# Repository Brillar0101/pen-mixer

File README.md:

# Pen Mixer

Pen Mixer is a small motion controller that clips onto the top of an ordinary
pen and turns handwriting gestures into live audio control. An IMU on the
board reads tilt and twist, an nRF52840 sends the motion to a laptop over
Bluetooth, and the laptop shapes whatever track is playing: tilt the pen and
a filter sweeps, twist it and the level moves. The better your pen control
gets, the better your mix sounds.

<p align="center"><em>The v2.1 board (13 &times; 35 mm) in its clear case</em></p>

This repo holds the whole project: prototype firmware, production firmware and
laptop stack, and the production PCB as a KiCad project.

```mermaid
flowchart LR
    HAND["Hand<br>tilt, twist"] --> FW

    subgraph pen["Pen Mixer board: on the pen"]
        FW["LSM6DS3TR-C IMU<br>+ ISP1807 nRF52840"]
    end

    FW -->|"BLE, Nordic UART"| BR
    FW -.->|"USB-C, serial"| BR

    subgraph laptop["Laptop"]
        BR["bridge.py<br>smooth, map"] -->|"UDP"| PD["Pure Data<br>filter + gain"]
        BR -->|"SSE"| DASH["dashboard<br>localhost:8080"]
    end

    PD --> SPK["Speakers"]

    classDef pfBlue fill:#E7F1FA,stroke:#0066CC,color:#151515
    classDef pfGold fill:#FDF7E7,stroke:#F0AB00,color:#151515
    classDef pfGreen fill:#F3FAF2,stroke:#3E8635,color:#151515
    classDef pfGray fill:#F0F0F0,stroke:#6A6E73,color:#151515
    class HAND,SPK pfBlue
    class FW pfGreen
    class BR pfGold
    class PD,DASH pfGray
```

## The hardware

Two production board shapes exist. v2.1 is a 13 x 35 mm bar (frozen in
`production/kicad/v2/`). v3, the current design in `production/kicad/`, is a
regular five-point star 40 mm tip to tip with a vertical, top-entry USB-C
(G-Switch GT-USB-7055E) in the body so all five prongs are identical, the
antenna at the top tip, LEDs out on the left arm and the button in the right
arm; otherwise the same parts and the same four-layer 0.8 mm stack. The v2.1 board is a 13 x 35 mm, four-layer, 0.8 mm PCB, all SMD, designed
to ride on a pen barrel with a 401230 LiPo at the back of the pen.

| Ref | Part | Role |
|---|---|---|
| U1 | ISP1807 | nRF52840 with integrated antenna, pre-certified |
| U2 | LSM6DS3TR-C | 6-axis IMU |
| U3 | MCP73831 | LiPo charger, 50 mA |
| U4 | TPS7A02 | 3.3 V LDO, 200 nA quiescent |
| J1 | USB-C 16P | charge, programming, serial |
| J2 | pads on B.Cu | off-board LiPo, 401230 |

The KiCad project lives in `production/`. Schematic PDF, board plots, a render
and the BOM are in `production/output/`.

The board is fully routed and fabrication-ready: 0 unrouted connections,
ground pours on all four layers, and a clean DRC. U1 sits on the official
JLCPCB land pattern with part-for-part verified pad geometry, and every
component carries the 3D model of the exact part being ordered.

Every pinout came from a primary datasheet, kept in `production/datasheets/`.
The one that would have cost a board spin: ISP1807 pin 20 (OUT_ANT) must be
tied to pin 22 (OUT_MOD) on the application PCB, or the radio has no antenna.

## The firmware and laptop stack

`prototype/` runs on the Seeed XIAO nRF52840 Sense today and targets the
custom board unchanged, since both are an nRF52840 with an ST IMU on I2C.

```
prototype/
  bridge.py           serial or BLE, then smoothing, mapping, UDP, dashboard
  ble_source.py       laptop-side BLE client for --ble
  dashboard.py        live web view on :8080
  firmware/
    code.py           IMU over USB serial
    code_ble.py       IMU over BLE, advertises as PenMixer-Lexy
  patches/            Pure Data: track playback, manual sliders, live input
```

How to run all of it, from firmware to Pure Data to the dashboard, lives in
[docs/RUNNING.md](docs/RUNNING.md).

## Run the desktop app

The Qt app in `app/` is the laptop side: it EQs whatever the computer is
playing, driven by the pen over Bluetooth. Full detail, Docker, and
troubleshooting are in `app/README.md`; the short version:

### macOS

```bash
brew install blackhole-2ch switchaudio-osx       # first time only
git clone https://github.com/Brillar0101/pen-mixer.git
cd pen-mixer/app
python3 -m venv venv
venv/bin/pip install -r requirements.txt -e .    # first time only
venv/bin/python -m penmixer.app                  # every time
```

In the window: click "Route system audio here", set Source to "Bluetooth
(pen board)" or use "Scan Bluetooth", play music, move the pen. Closing the
app restores your speakers.

### Windows

First time only, in an administrator PowerShell, then reboot (VB-CABLE is
the Windows loopback device):

```powershell
curl.exe -L -o $env:TEMP\vbcable.zip https://download.vb-audio.com/Download_CABLE/VBCABLE_Driver_Pack45.zip
Expand-Archive $env:TEMP\vbcable.zip $env:TEMP\vbcable -Force
& $env:TEMP\vbcable\VBCABLE_Setup_x64.exe
shutdown /r /t 0
```

Then in a normal PowerShell:

```powershell
git clone https://github.com/Brillar0101/pen-mixer.git
cd pen-mixer\app
python -m venv venv
venv\Scripts\pip install -r requirements.txt -e .   # first time only
venv\Scripts\python -m penmixer.app                 # every time
```

Set Settings > System > Sound > Output to "CABLE Input", then in the window
click "Hear music here", set Source to "Bluetooth (pen board)", play music,
move the pen. Set the output back to your speakers when done.

No board? Set Source to "Simulate (no board)".

## Measured, not estimated

| What | Number |
|---|---|
| Frame rate over USB | 197 Hz against a 250 Hz target |
| Frames in the soak run | 105,872, 0 malformed |
| Smoother settling, alpha 0.4 | 24 ms to 95% of a step |
| End-to-end budget | 32 ms, against ~20 ms where feel degrades |
| BLE vs USB link cost | ~10 ms vs 1 ms |

## Layout

```
prototype/            nRF52840 Sense build: real IMU, USB or BLE, laptop stack
app/                  Qt desktop app: 3-band EQ, visualizer, one-window stack
                      (start instructions for macOS and Windows: app/README.md)
production/           the production board
  kicad/              KiCad 10 project, footprints, 3D models
  datasheets/         primary sources for every pinout
  output/             schematic PDF, board plots, render, BOM, DRC report
docs/                 architecture, run guide, requirements (PRD)
ARCHITECTURE.md       how it all fits together, with diagrams
```

## License

MIT. See [LICENSE](LICENSE).

Built by Barakaeli ([Brillar0101](https://github.com/Brillar0101)) and
Lexy ([vnllagoldfish](https://github.com/vnllagoldfish)).

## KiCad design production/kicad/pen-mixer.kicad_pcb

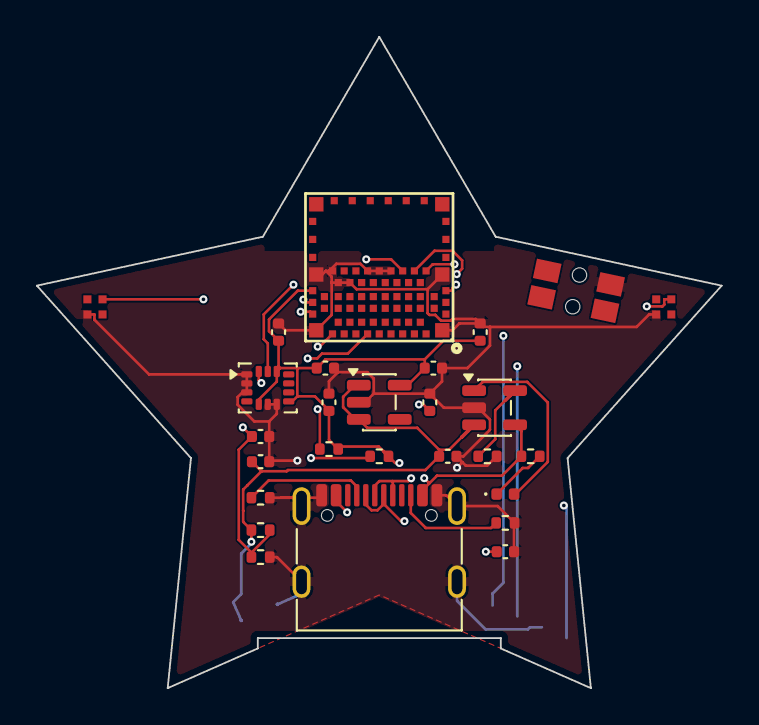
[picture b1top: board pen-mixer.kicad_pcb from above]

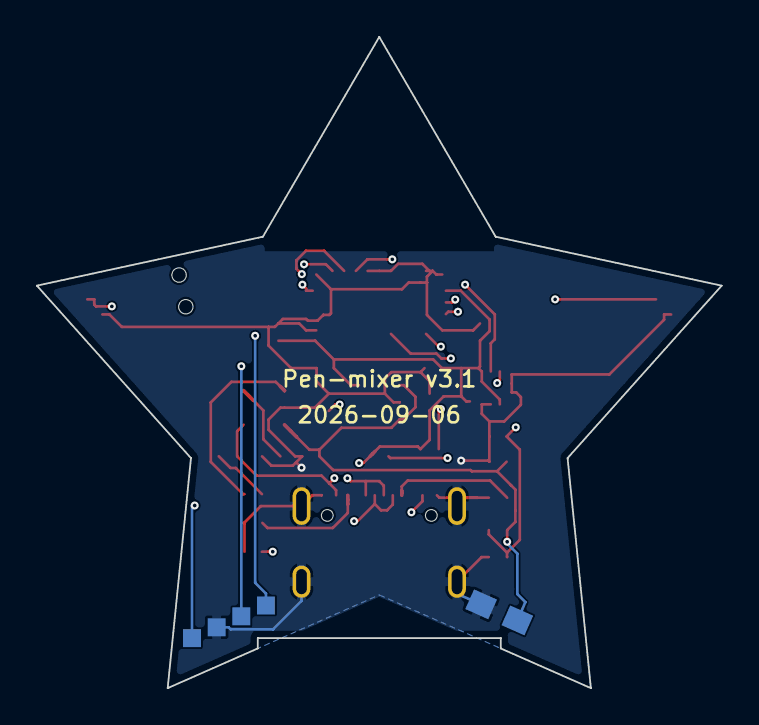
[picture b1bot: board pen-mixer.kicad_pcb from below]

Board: 4 copper layers, 38.0 x 36.2 mm, 32 parts (5 on the bottom side), 16 nets.

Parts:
C1, C2: 4u7; C_0402_1005Metric
C3, C4: 1u; C_0402_1005Metric
C5, C7, C8, C10, C11: 100n; C_0402_1005Metric
C6: 10u; C_0402_1005Metric
D1: GRN; LED_0402_1005Metric
J1: USB-C 16P; GT-USB-7010ASV
J2: BAT; SolderPad_1.2x2.0mm
LED1, LED2: XL-1010RGBC; LED-SMD_4P-L1.0-W1.0-TL_XL-1010RGBC-WS2812B
R1, R2: 5k1; R_0402_1005Metric
R3: 20k; R_0402_1005Metric
R4: 1k; R_0402_1005Metric
R6, R7: 4k7; R_0402_1005Metric
R8, R9: 1M; R_0402_1005Metric
SW1: EVQP7C01P; SW-SMD_EVQP7C01P
TP1: SWDIO; TestPad_1.0mm
TP2: SWDCLK; TestPad_1.0mm
TP4: GND; TestPad_1.0mm
TP5: +3V3; TestPad_1.0mm
U1: ISP1807-LR; BULETM-SMD_ISP1807
U2: LSM6DS3TR-C; LGA-14_3x2.5mm_P0.5mm_LayoutBorder3x4y
U3: MCP73831T-2ACI/OT; SOT-23-5
U4: TPS7A0533PDBV; SOT-23-5

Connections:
+3V3: C4.1, C5.1, C6.1, C7.1, C8.1, R6.2, R7.2, TP5.1, U1.26, U2.5, U2.8, U2.12, U4.5
CC1: J1.A5, R1.1
CC2: J1.B5, R2.1
CHG_STAT: D1.2, U3.1
GND: C1.2, C2.2, C3.2, C4.2, C5.2, C6.2, C7.2, C8.2, C10.2, C11.2, J1.A1, J1.A12, J1.B1, J1.B12, J1.SH, J2.2, LED1.3, LED2.3, R1.2, R2.2, R3.2, R9.2, SW1.2, TP4.1, U1.1, U1.7, U1.14, U1.16, U1.18, U1.21, U1.23, U1.24, U1.25, U1.31, U2.1, U2.2, U2.3, U2.6, U2.7, U3.2, U4.2
IPROG: R3.1, U3.5
LED_A: D1.1, R4.2
SCL: R7.1, U1.6, U2.13
SDA: R6.1, U1.32, U2.14
SWDCLK: TP2.1, U1.30
SWDIO: TP1.1, U1.28
USB_DM: J1.A7, J1.B7, U1.10
USB_DP: J1.A6, J1.B6, U1.8
VBAT: C2.1, C3.1, C11.1, J2.1, LED1.2, LED2.2, R8.1, U3.3, U4.1, U4.3
VBAT_SENSE: C10.1, R8.2, R9.1, U1.38
VBUS: C1.1, J1.A4, J1.A9, J1.B4, J1.B9, R4.1, U1.12, U3.4

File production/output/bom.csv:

"Reference","Value","Footprint","QUANTITY"
"C1,C2","4u7","Capacitor_SMD:C_0402_1005Metric","2"
"C3,C4","1u","Capacitor_SMD:C_0402_1005Metric","2"
"C5,C7-C10","100n","Capacitor_SMD:C_0402_1005Metric","5"
"C6","10u","Capacitor_SMD:C_0402_1005Metric","1"
"D1","GRN","LED_SMD:LED_0402_1005Metric","1"
"J1","USB-C 16P","Connector_USB:USB_C_Receptacle_G-Switch_GT-USB-7010ASV","1"
"J2","BAT","pen-mixer:SolderPad_1.2x2.0mm","1"
"J3","FSR","pen-mixer:SolderPad_1.2x2.0mm","1"
"R1,R2","5k1","Resistor_SMD:R_0402_1005Metric","2"
"R3","20k","Resistor_SMD:R_0402_1005Metric","1"
"R4","1k","Resistor_SMD:R_0402_1005Metric","1"
"R5","10k","Resistor_SMD:R_0402_1005Metric","1"
"R6,R7","4k7","Resistor_SMD:R_0402_1005Metric","2"
"R8,R9","1M","Resistor_SMD:R_0402_1005Metric","2"
"TP1","SWDIO","pen-mixer:TestPad_1.0mm","1"
"TP2","SWDCLK","pen-mixer:TestPad_1.0mm","1"
"TP4","GND","pen-mixer:TestPad_1.0mm","1"
"TP5","+3V3","pen-mixer:TestPad_1.0mm","1"
"U1","ISP1807-LR","pen-mixer:ISP1807-LR","1"
"U2","LSM6DS3TR-C","Package_LGA:LGA-14_3x2.5mm_P0.5mm_LayoutBorder3x4y","1"
"U3","MCP73831T-2ACI/OT","Package_TO_SOT_SMD:SOT-23-5","1"
"U4","TPS7A0533PDBV","Package_TO_SOT_SMD:SOT-23-5","1"

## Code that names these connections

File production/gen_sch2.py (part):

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    pw("GND",e[0],e[1],180 if d[1]>0 else 0)
v=P("U1","12"); w(v,(v[0],v[1]-2.54)); pw("VBUS",v[0],v[1]-2.54)
c=P("U1","26"); w(c,(c[0],c[1]+2.54)); pw("+3V3",c[0],c[1]+2.54,180)
for pin,net in (("8","USB_DP"),("10","USB_DM")):
    q=P("U1",pin); w(q,(q[0],q[1]+3.81)); glab(net,q[0],q[1]+3.81,270)
for pin,net in (("28","SWDIO"),("30","SWDCLK"),("6","SCL")):
    q=P("U1",pin); w(q,(q[0]+3.81,q[1])); glab(net,q[0]+3.81,q[1],0)
for pin,net in (("32","SDA"),("2","IMU_INT1"),("4","IMU_INT2"),
                ("36","FSR_SENSE"),("38","VBAT_SENSE")):
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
